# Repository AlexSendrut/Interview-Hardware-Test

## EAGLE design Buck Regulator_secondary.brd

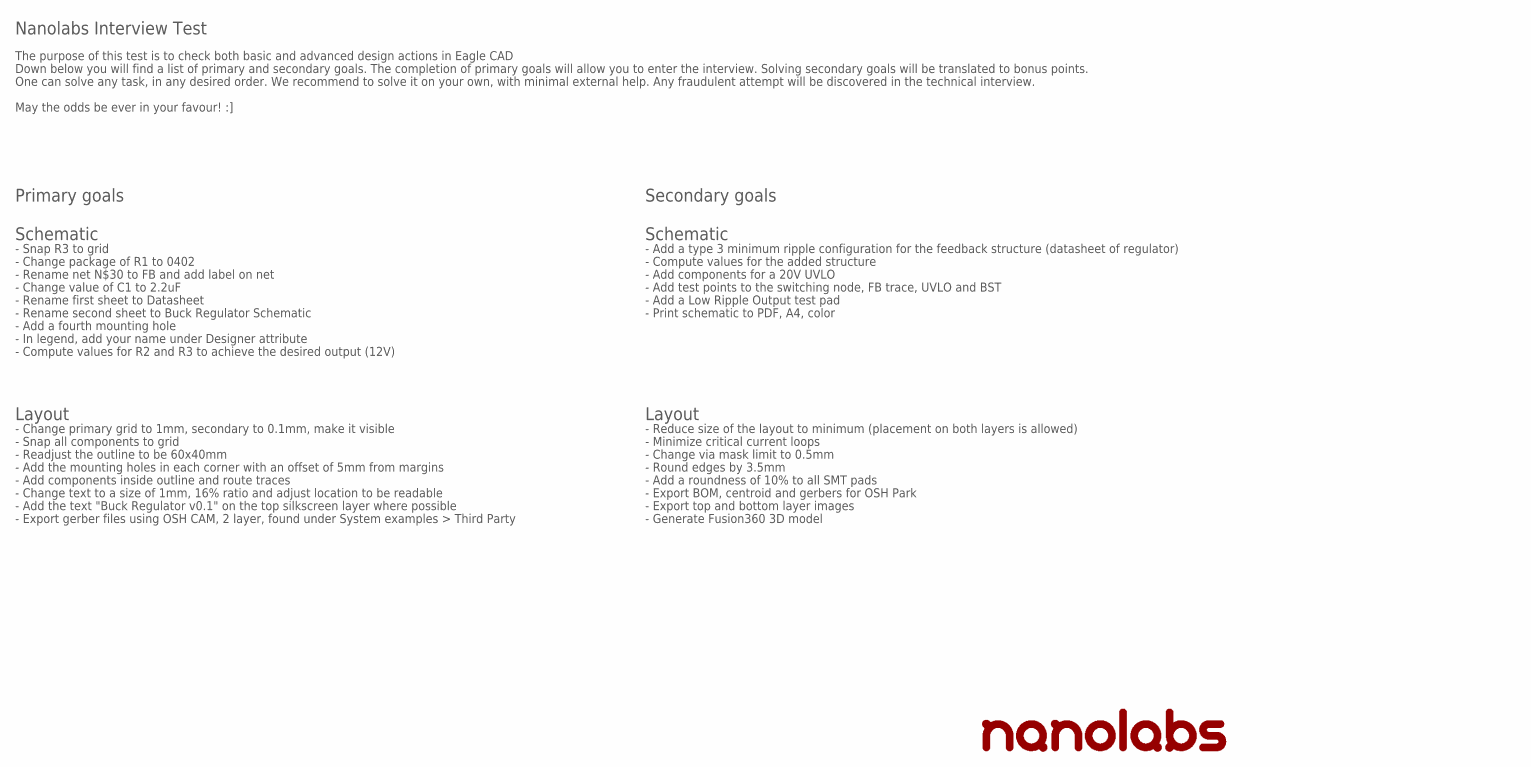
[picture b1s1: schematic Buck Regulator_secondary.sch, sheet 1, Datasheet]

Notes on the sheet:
Nanolabs Interview Test
The purpose of this test is to check both basic and advanced design actions in Eagle CAD
Down below you will find a list of primary and secondary goals. The completion of primary goals will allow you to enter the interview. Solving secondary goals will be translated to bonus points.
One can solve any task, in any desired order. We recommend to solve it on your own, with minimal external help. Any fraudulent attempt will be discovered in the technical interview.
May the odds be ever in your favour! :]
Primary goals
Secondary goals
- Snap R3 to grid
- Change package of R1 to 0402
- Rename net N$30 to FB and add label on net
- Rename first sheet to Datasheet
- Rename second sheet to Buck Regulator Schematic
- Add a fourth mounting hole
- In legend, add your name under Designer attribute
- Change value of C1 to 2.2uF
Schematic
- Change primary grid to 1mm, secondary to 0.1mm, make it visible
Layout
- Snap all components to grid
- Readjust the outline to be 60x40mm
- Add the mounting holes in each corner with an offset of 5mm from margins
- Add components inside outline and route traces
- Change text to a size of 1mm, 16% ratio and adjust location to be readable
- Add the text "Buck Regulator v0.1" on the top silkscreen layer where possible
- Export gerber files using OSH CAM, 2 layer, found under System examples > Third Party
- Add a type 3 minimum ripple configuration for the feedback structure (datasheet of regulator)
- Compute values for R2 and R3 to achieve the desired output (12V)
- Compute values for the added structure
- Add components for a 20V UVLO
- Add test points to the switching node, FB trace, UVLO and BST
- Add a Low Ripple Output test pad
- Reduce size of the layout to minimum (placement on both layers is allowed)
- Minimize critical current loops
- Change via mask limit to 0.5mm
- Round edges by 3.5mm
- Add a roundness of 10% to all SMT pads
- Export BOM, centroid and gerbers for OSH Park
- Print schematic to PDF, A4, color
- Export top and bottom layer images
- Generate Fusion360 3D model

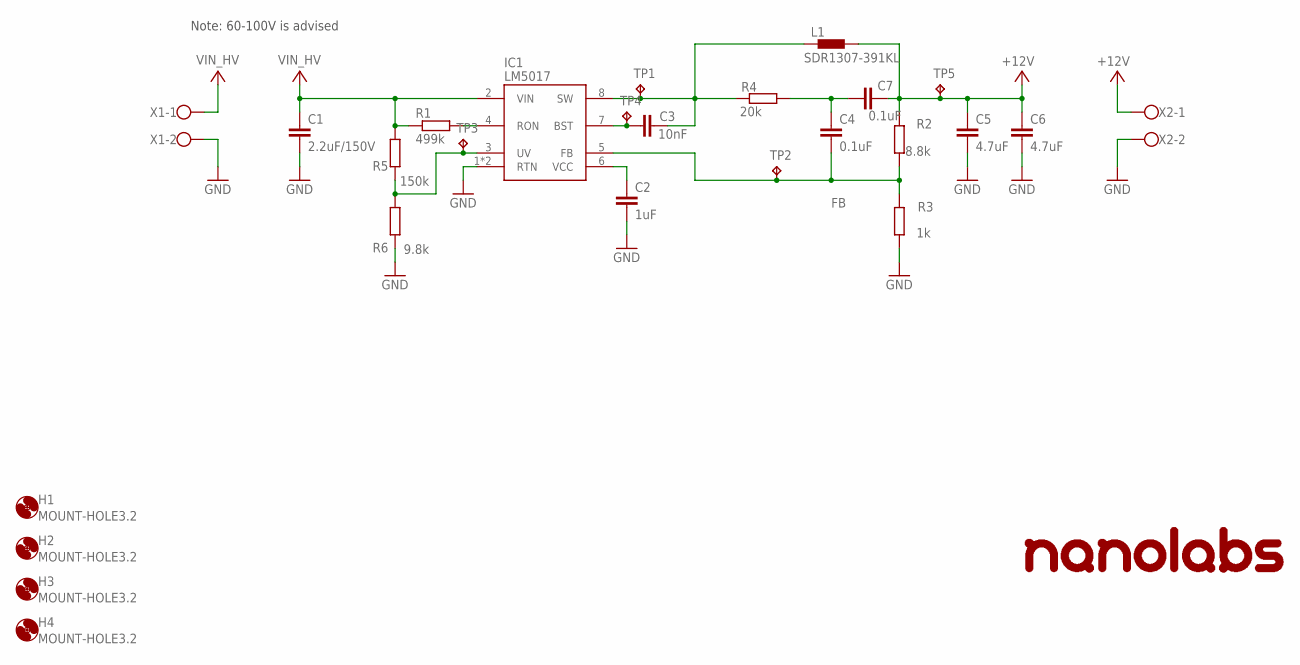
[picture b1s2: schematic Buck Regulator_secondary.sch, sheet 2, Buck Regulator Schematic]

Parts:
C1: 2.2uF/150V; C1812
C2: 1uF; C0603
C3: 10nF; C0603
C4, C7: 0.1uF; C0603
C5, C6: 4.7uF; C0603
H1, H2, H3, H4: MOUNT-HOLE3.2; 3,2
IC1: LM5017; SO-08-EP
L1: SDR1307-391KL
R1: 499k; R0402
R2: 8.8k; R0603
R3: 1k; R0603
R4: 20k; R0603
R5: 150k; R0402
R6: 9.8k; R0402
TP1, TP2, TP3, TP4, TP5: TPB1,27; B1,27
X1, X2: W237-102

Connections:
+12V: C5.1, C6.1, C7.2, L1.2, R2.2, TP5.TP, X2.1
FB: C4.2, IC1.5 (FB), R2.1, R3.2, TP2.TP
GND: C1.2, C2.2, C5.2, C6.2, IC1.1 (RTN), IC1.9 (RTN), R3.1, R6.1, X1.2, X2.2
unnamed: C4.1, C7.1, R4.1
unnamed: IC1.3 (UV), R5.1, R6.2, TP3.TP
unnamed: C2.1, IC1.6 (VCC)
unnamed: C3.1, IC1.7 (BST), TP4.TP
unnamed: C3.2, IC1.8 (SW), L1.1, R4.2, TP1.TP
unnamed: IC1.4 (RON), R1.2
VIN_HV: C1.1, IC1.2 (VIN), R1.1, R5.2, X1.1

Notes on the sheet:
Note: 60-100V is advised

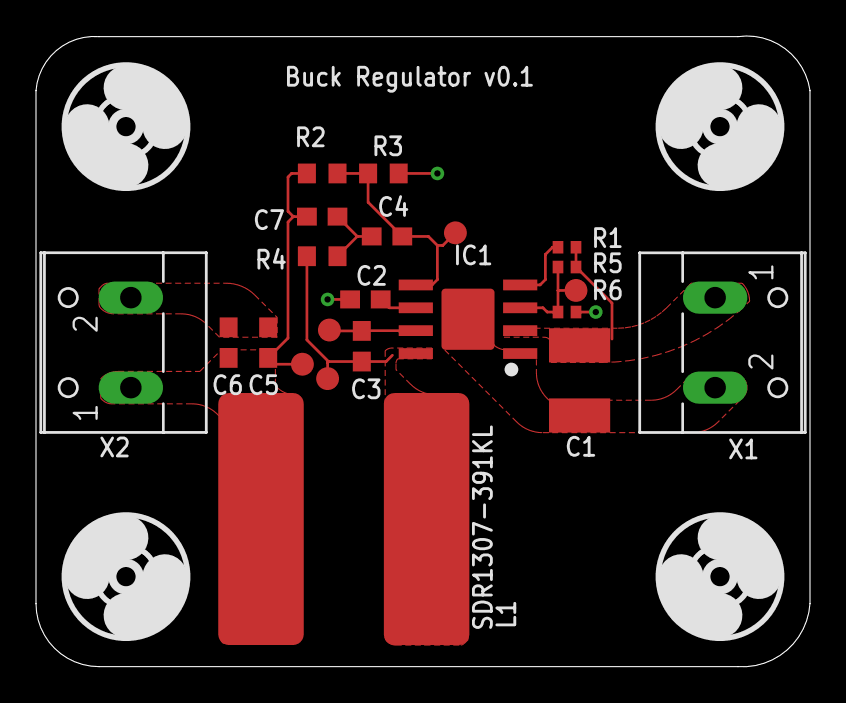
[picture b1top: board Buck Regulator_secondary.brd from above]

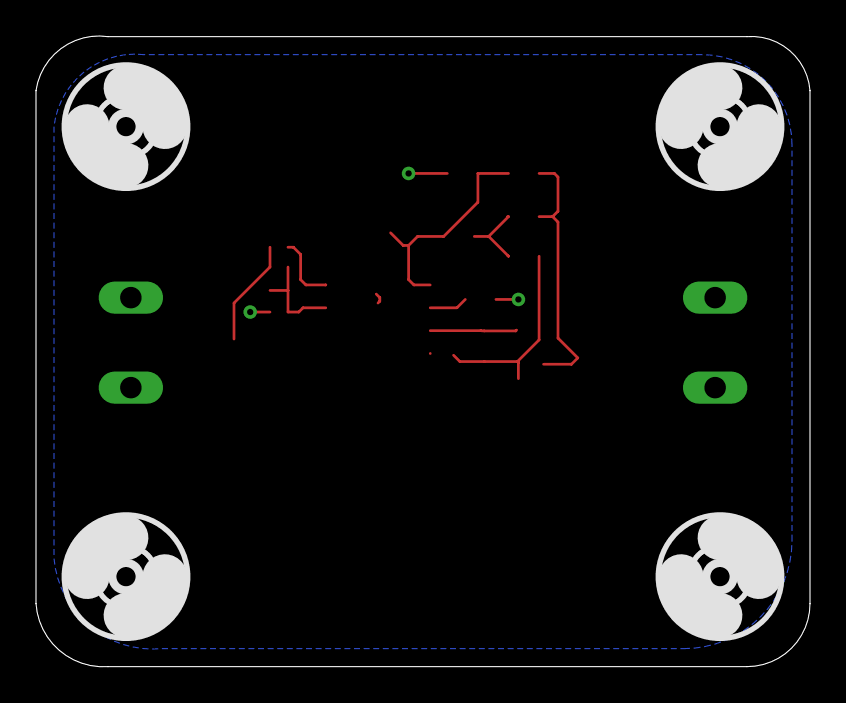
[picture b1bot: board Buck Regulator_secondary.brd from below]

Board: 2 copper layers, 43.0 x 35.0 mm, 26 parts (3 on the bottom side), 10 nets.

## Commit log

2021-08-01 initial-commit
